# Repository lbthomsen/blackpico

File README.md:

# blackpico
Raspberry Pi RP2040 Development Board

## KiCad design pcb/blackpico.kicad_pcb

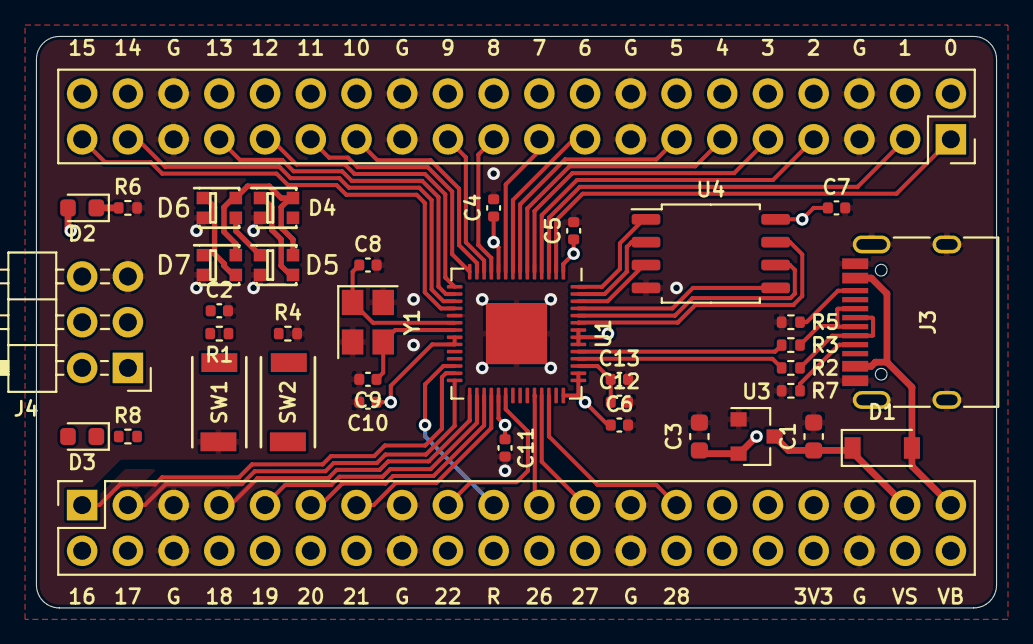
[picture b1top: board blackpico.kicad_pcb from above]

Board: 4 copper layers, 53.3 x 31.8 mm, 38 parts (0 on the bottom side), 59 nets.

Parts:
C1, C3: 10uF; C_0603_1608Metric
C2, C4, C5, C6, C7, C10, C11, C13: 100nF; C_0402_1005Metric
C8, C9: 15pF; C_0402_1005Metric
C12: 2.2uF; C_0402_1005Metric
D1: D_SOD-123
D2: GRE; LED_0603_1608Metric
D3: BLUE; LED_0603_1608Metric
D4, D5, D6, D7: WS2812B; WS2812B-2020
J1, J2: PinSocket_2x20_P2.54mm_Vertical_Stackable
J3: USB-C; USB_C_Receptacle_HRO_TYPE-C-31-M-12
J4: PinHeader_2x03_P2.54mm_Horizontal
R1, R4: 10k; R_0402_1005Metric
R2, R3: 22R; R_0402_1005Metric
R5, R7: 5.1k; R_0402_1005Metric
R6, R8: 220; R_0402_1005Metric
SW1, SW2: TS-1088R-02526
U1: RP2040; QFN-56-1EP_7x7mm_P0.4mm_EP3.4x3.4mm
U3: XC6206P332MR; SOT-23
U4: W25Q128JVSIQ; SOIC-8_5.23x5.23mm_P1.27mm
Y1: 12MHz; Crystal_SMD_3225-4Pin_3.2x2.5mm

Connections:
+1V1: C12.1, C13.1, U1.45
+3V3: C3.1, C4.1, C5.1, C6.1, C7.1, C10.1, C11.1, D2.2, D3.2, D4.4, D5.4, D6.4, D7.4, J2.31, J2.32, J4.2, R1.1, SW2.2, U1.1, U1.10, U1.22, U1.23, U1.33, U1.42, U1.43, U1.44, U1.48, U1.49, U1.50, U3.2, U4.8
ADC_VREF: J2.29, J2.30
BO0: R4.1, SW2.1
D+: R3.2, U1.47
D-: R2.2, U1.46
GND: C1.2, C2.2, C3.2, C4.2, C5.2, C6.2, C7.2, C8.2, C9.2, C10.2, C11.2, C12.2, C13.2, D4.2, D5.2, D6.2, D7.2, J1.5, J1.6, J1.15, J1.16, J1.25, J1.26, J1.35, J1.36, J2.5, J2.6, J2.15, J2.16, J2.25, J2.26, J2.35, J2.36, J3.A1, J3.A12, J3.B1, J3.B12, J3.S1, J4.5, R4.2, R5.2, R6.2, R7.2, SW1.1, U1.19, U1.57, U3.1, U4.4, Y1.2, Y1.4
IO0: J1.1, J1.2, U1.2
IO1: J1.3, J1.4, U1.3
IO2: J1.7, J1.8, U1.4
IO3: J1.9, J1.10, U1.5
IO4: J1.11, J1.12, U1.6
IO5: J1.13, J1.14, U1.7
IO6: J1.17, J1.18, U1.8
IO7: J1.19, J1.20, U1.9
IO8: J1.21, J1.22, U1.11
IO9: J1.23, J1.24, U1.12
IO10: J1.27, J1.28, U1.13
IO11: J1.29, J1.30, U1.14
IO12: J1.31, J1.32, U1.15
IO13: J1.33, J1.34, U1.16
IO14: J1.37, J1.38, U1.17
IO15: J1.39, J1.40, U1.18
IO16: J2.1, J2.2, U1.27
IO17: J2.3, J2.4, U1.28
IO18: J2.7, J2.8, U1.29
IO19: J2.9, J2.10, U1.30
IO20: J2.11, J2.12, U1.31
IO21: J2.13, J2.14, U1.32
IO22: J2.17, J2.18, U1.34
IO26: J2.21, J2.22, U1.38
IO27: J2.23, J2.24, U1.39
IO28: J2.27, J2.28, U1.40
LED: R8.2, U1.36
unnamed: D2.1, R6.1
unnamed: D3.1, R8.1
unnamed: D4.1, D5.3
unnamed: D5.1, D6.3
unnamed: D6.1, D7.3
unnamed: J2.33, J2.34
unnamed: J3.A5, R7.1
unnamed: J3.A6, J3.B6, R3.1
unnamed: J3.A7, J3.B7, R2.1
unnamed: J3.B5, R5.1
QCK: U1.52, U4.6
QD0: U1.53, U4.5
QD1: U1.55, U4.2
QD2: U1.54, U4.3
QD3: U1.51, U4.7
QSS: U1.56, U4.1
RGB: D4.3, U1.35
RST: C2.1, J4.1, R1.2, SW1.2
RUN: J2.19, J2.20, U1.26
SWCLK: J4.3, U1.24
SWDIO: J4.4, U1.25
VBUS: D1.2, J2.39, J2.40, J3.A4, J3.A9, J3.B4, J3.B9
VDC: C1.1, D1.1, J2.37, J2.38, U3.3
XI: C8.1, U1.20, Y1.1
XO: C9.1, U1.21, Y1.3

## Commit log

2021-12-19 Hmmm
2021-12-19 Hmmmm
2021-12-19 Hmmmmm
2021-12-30 Removed bak files

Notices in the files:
pcb/blackpico.kicad_pcb:
(C) 2021 Lars Boegild Thomsen
